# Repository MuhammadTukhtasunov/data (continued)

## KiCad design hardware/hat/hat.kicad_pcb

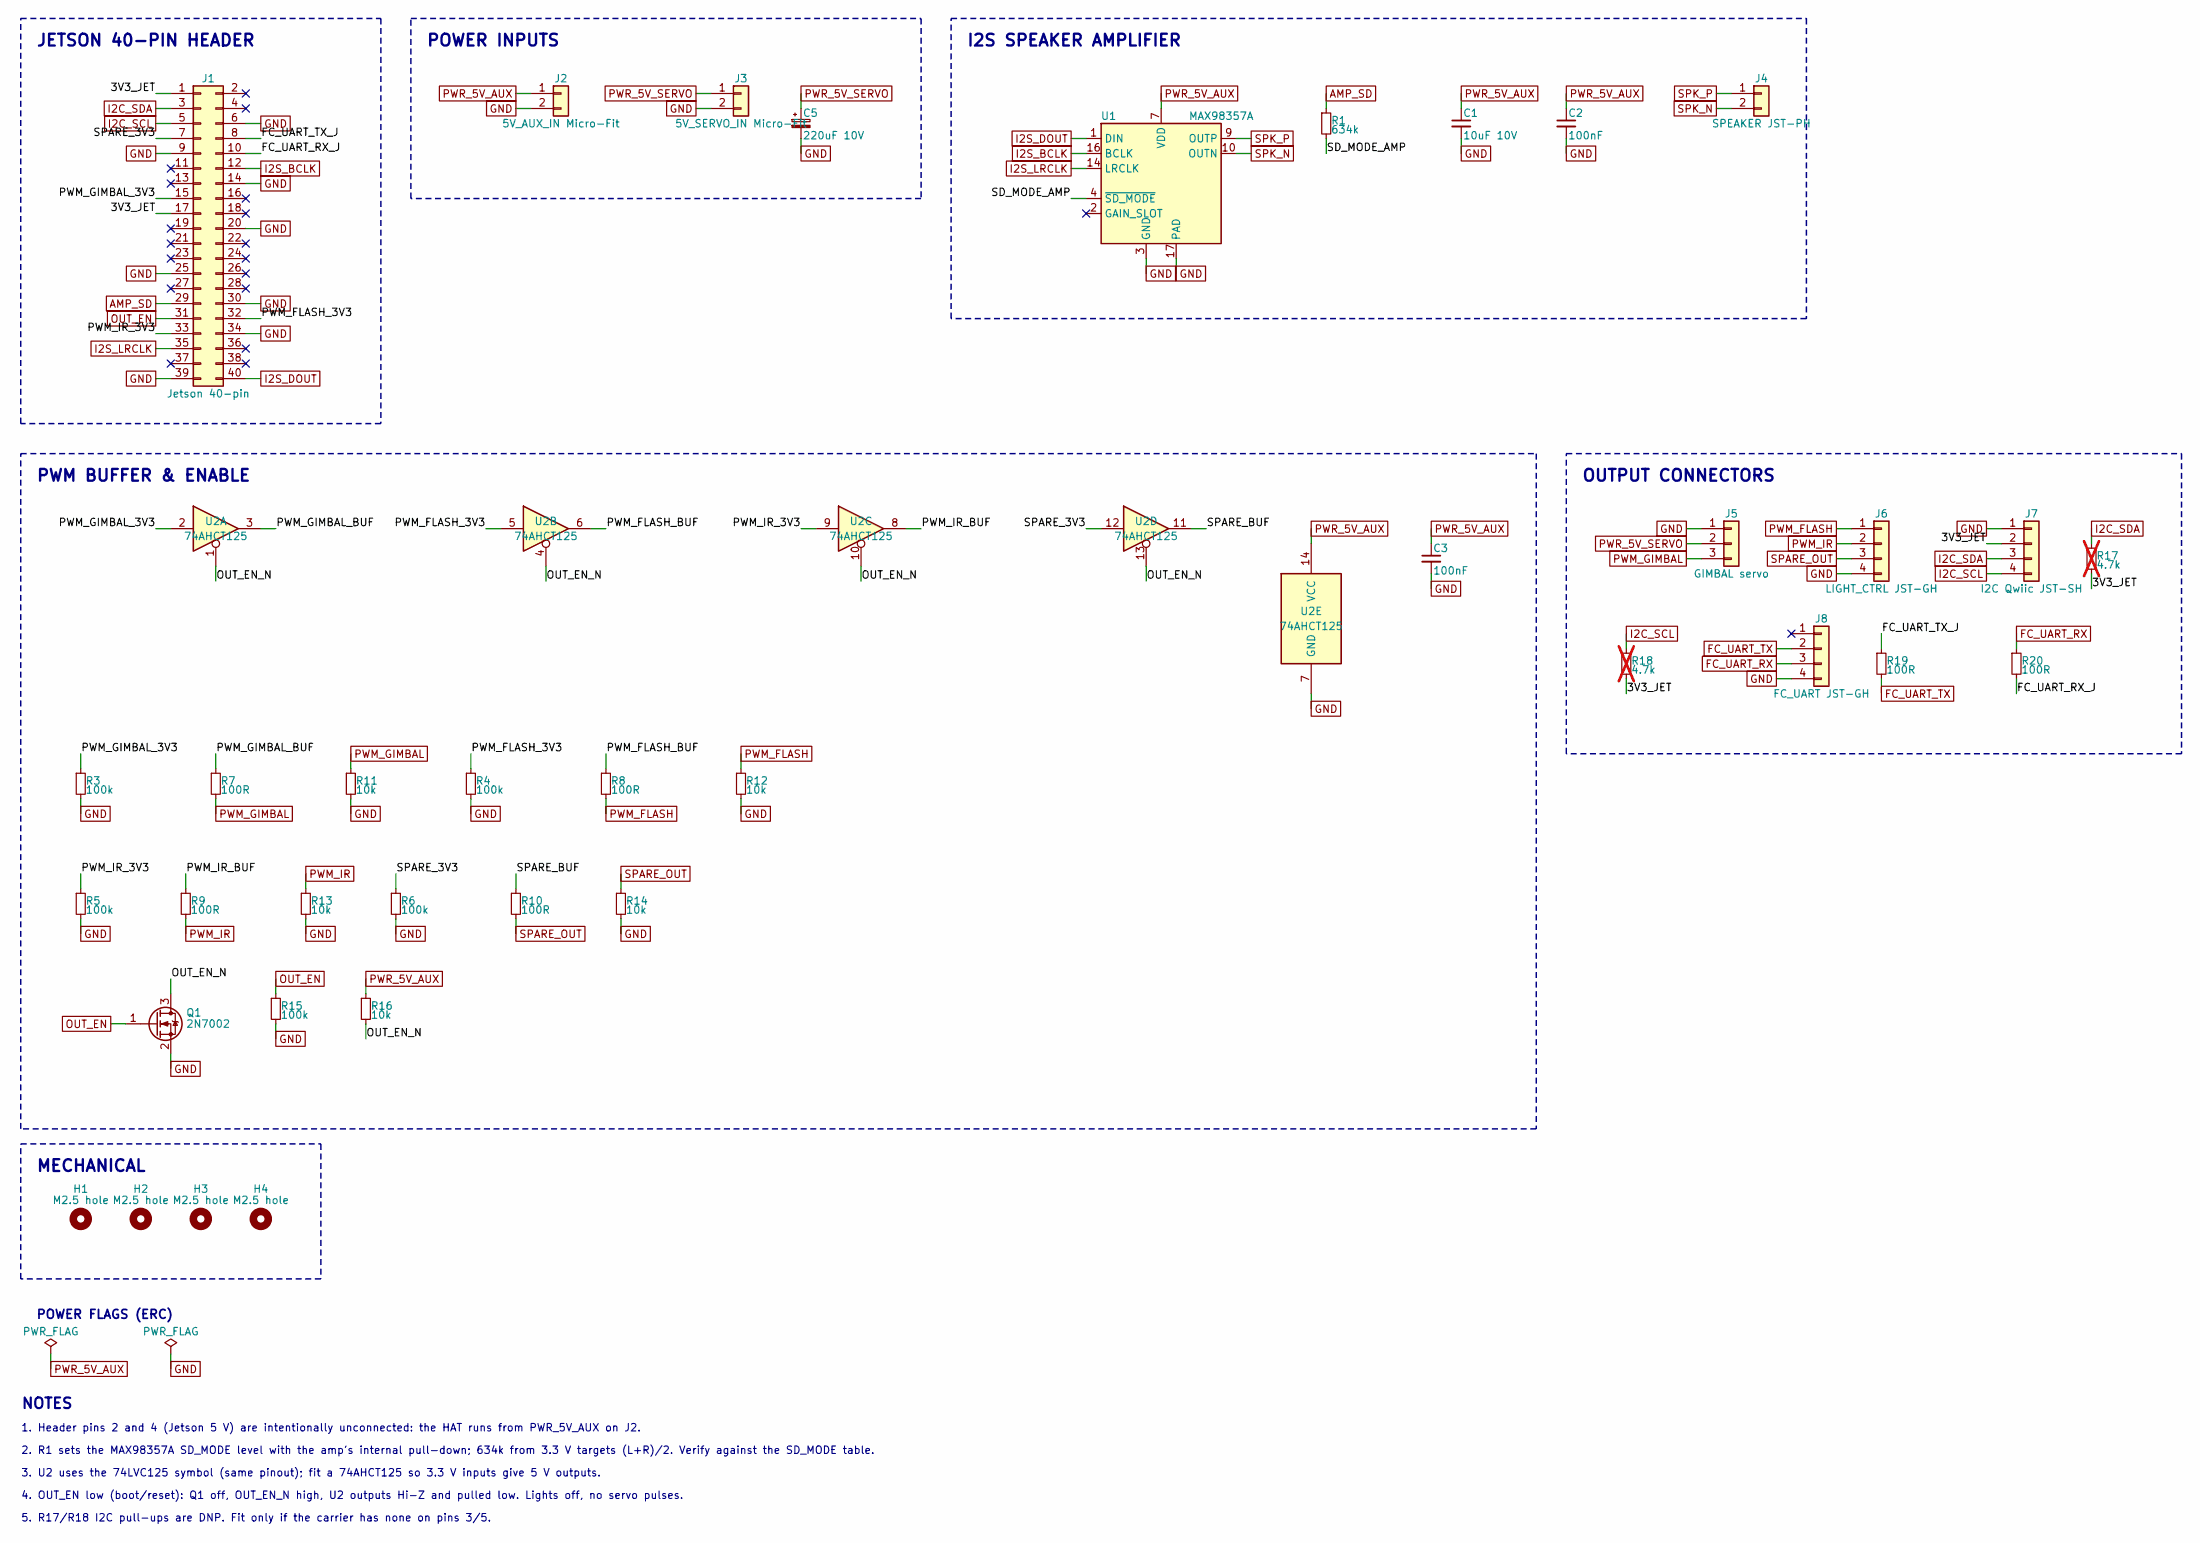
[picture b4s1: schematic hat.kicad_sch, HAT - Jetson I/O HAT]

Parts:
C1: 10uF 10V; C_0805_2012Metric
C2, C3: 100nF; C_0603_1608Metric
C5: 220uF 10V; CP_Elec_8x10.5
H1, H2, H3, H4: M2.5 hole; MountingHole_2.7mm_M2.5
J1: Jetson 40-pin; PinSocket_2x20_P2.54mm_Vertical
J2: 5V_AUX_IN Micro-Fit; Molex_Micro-Fit_3.0_43650-0210_1x02-1MP_P3.00mm_Horizontal
J3: 5V_SERVO_IN Micro-Fit; Molex_Micro-Fit_3.0_43650-0210_1x02-1MP_P3.00mm_Horizontal
J4: SPEAKER JST-PH; JST_PH_S2B-PH-K_1x02_P2.00mm_Horizontal
J5: GIMBAL servo; PinHeader_1x03_P2.54mm_Vertical
J6: LIGHT_CTRL JST-GH; JST_GH_SM04B-GHS-TB_1x04-1MP_P1.25mm_Horizontal
J7: I2C Qwiic JST-SH; JST_SH_SM04B-SRSS-TB_1x04-1MP_P1.00mm_Horizontal
J8: FC_UART JST-GH; JST_GH_SM04B-GHS-TB_1x04-1MP_P1.25mm_Horizontal
Q1: 2N7002; SOT-23
R1: 634k; R_0603_1608Metric
R3, R4, R5, R6, R15: 100k; R_0603_1608Metric
R7, R8, R9, R10, R19, R20: 100R; R_0603_1608Metric
R11, R12, R13, R14, R16: 10k; R_0603_1608Metric
R17, R18: 4.7k; R_0603_1608Metric; not fitted
U1: MAX98357A; TQFN-16-1EP_3x3mm_P0.5mm_EP1.23x1.23mm
U2: 74AHCT125; SOIC-14_3.9x8.7mm_P1.27mm

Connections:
3V3_JET: J1.1, J1.17, J7.2, R17.2, R18.2
AMP_SD: J1.29, R1.1
FC_UART_RX: J8.3, R20.1
FC_UART_RX_J: J1.10, R20.2
FC_UART_TX: J8.2, R19.2
FC_UART_TX_J: J1.8, R19.1
GND: C1.2, C2.2, C3.2, C5.2, J1.6, J1.9, J1.14, J1.20, J1.25, J1.30, J1.34, J1.39, J2.2, J3.2, J5.1, J6.4, J7.1, J8.4, Q1.2 (S), R3.2, R4.2, R5.2, R6.2, R11.2, R12.2, R13.2, R14.2, R15.2, U1.3 (GND), U1.11 (GND), U1.15 (GND), U1.17 (PAD), U2.7 (GND)
I2C_SCL: J1.5, J7.4, R18.1
I2C_SDA: J1.3, J7.3, R17.1
I2S_BCLK: J1.12, U1.16 (BCLK)
I2S_DOUT: J1.40, U1.1 (DIN)
I2S_LRCLK: J1.35, U1.14 (LRCLK)
OUT_EN: J1.31, Q1.1 (G), R15.1
OUT_EN_N: Q1.3 (D), R16.2, U2.1, U2.4, U2.10, U2.13
PWM_FLASH: J6.1, R8.2, R12.1
PWM_FLASH_3V3: J1.32, R4.1, U2.5
PWM_FLASH_BUF: R8.1, U2.6
PWM_GIMBAL: J5.3, R7.2, R11.1
PWM_GIMBAL_3V3: J1.15, R3.1, U2.2
PWM_GIMBAL_BUF: R7.1, U2.3
PWM_IR: J6.2, R9.2, R13.1
PWM_IR_3V3: J1.33, R5.1, U2.9
PWM_IR_BUF: R9.1, U2.8
PWR_5V_AUX: C1.1, C2.1, C3.1, J2.1, R16.1, U1.7 (VDD), U1.8 (VDD), U2.14 (VCC)
PWR_5V_SERVO: C5.1, J3.1, J5.2
SD_MODE_AMP: R1.2, U1.4 (~SD_MODE)
SPARE_3V3: J1.7, R6.1, U2.12
SPARE_BUF: R10.1, U2.11
SPARE_OUT: J6.3, R10.2, R14.1
SPK_N: J4.2, U1.10 (OUTN)
SPK_P: J4.1, U1.9 (OUTP)

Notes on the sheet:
JETSON 40-PIN HEADER
POWER INPUTS
I2S SPEAKER AMPLIFIER
PWM BUFFER & ENABLE
OUTPUT CONNECTORS
MECHANICAL
POWER FLAGS (ERC)
NOTES
1. Header pins 2 and 4 (Jetson 5 V) are intentionally unconnected: the HAT runs from PWR_5V_AUX on J2.
2. R1 sets the MAX98357A SD_MODE level with the amp's internal pull-down; 634k from 3.3 V targets (L+R)/2. Verify against the SD_MODE table.
3. U2 uses the 74LVC125 symbol (same pinout); fit a 74AHCT125 so 3.3 V inputs give 5 V outputs.
4. OUT_EN low (boot/reset): Q1 off, OUT_EN_N high, U2 outputs Hi-Z and pulled low. Lights off, no servo pulses.
5. R17/R18 I2C pull-ups are DNP. Fit only if the carrier has none on pins 3/5.

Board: 2 copper layers, 38 parts (0 on the bottom side), 31 nets, no tracks yet.

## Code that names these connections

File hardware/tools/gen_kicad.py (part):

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              # Raspberry-Pi-HAT style: header centred along the top edge, holes 3.5 mm in
              fixed={"J1": (90, 32.5, 3.5)}, hole_inset=3.5, pack_margin=(2.0, 8.5, 2.0, 7.0))
    b.notes = [
        "Header pins 2 and 4 (Jetson 5 V) are intentionally unconnected: the HAT runs from PWR_5V_AUX on J2.",
        "R1 sets the MAX98357A SD_MODE level with the amp's internal pull-down; 634k from 3.3 V targets (L+R)/2. Verify against the SD_MODE table.",
        "U2 uses the 74LVC125 symbol (same pinout); fit a 74AHCT125 so 3.3 V inputs give 5 V outputs.",
        "OUT_EN low (boot/reset): Q1 off, OUT_EN_N high, U2 outputs Hi-Z and pulled low. Lights off, no servo pulses.",
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    C(k, "C2", "10uF 10V", "PWR_5V_AUX", "GND", C0805)

    k = b.block("Teensy 4.1", cols=1)
    tp = {teensy_pin("VIN"): "PWR_5V_AUX", "1": "GND", "34": "GND", "47": "GND",
          "15": "3V3_T", "46": "3V3_T",
          teensy_pin("D18"): "SNS_SDA", teensy_pin("D19"): "SNS_SCL",
          teensy_pin("D2"): "GPIO2", teensy_pin("D3"): "GPIO3"}
    for n in range(1, 9):
        tp[teensy_pin(tx[n])] = f"TX{n}"
        tp[teensy_pin(rx[n])] = f"RX{n}_B"
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
    k = b.block("Expansion", cols=3)
    CONN(k, "J10", "EXP", "Connector_PinHeader_2.54mm:PinHeader_1x06_P2.54mm_Vertical",
         ["3V3_T", "GND", "SNS_SDA", "SNS_SCL", "GPIO2", "GPIO3"])
    R(k, "R41", "4.7k", "SNS_SDA", "3V3_T", dnp=True)
    R(k, "R42", "4.7k", "SNS_SCL", "3V3_T", dnp=True)

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
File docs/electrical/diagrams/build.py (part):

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    end''')
    e = d.edge
    e("P_I2S", "U1", "I2S_BCLK · I2S_LRCLK · I2S_DOUT", "i2s")
    e("P_AMP", "RSD", "AMP_SD", "gpio")
    e("RSD", "U1", "SD_MODE", "gpio")
    e("U1", "J4", "SPK_P / SPK_N (BTL)", "power")
    e("P_PWM", "RPD", "PWM_GIMBAL_3V3 · PWM_FLASH_3V3 · PWM_IR_3V3", "pwm")
    e("P_SP", "RPD", "SPARE_3V3", "gpio")
    e("RPD", "U2", "1A–4A", "pwm")
    e("P_EN", "Q1", "OUT_EN", "gpio")
    e("Q1", "U2", "OUT_EN_N → 1OE#–4OE#", "gpio")
    e("U2", "ROUT", "1Y–4Y (5 V)", "pwm")
    e("ROUT", "J5", "PWM_GIMBAL", "pwm")
    e("ROUT", "J6", "PWM_FLASH · PWM_IR · SPARE_OUT", "pwm")
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
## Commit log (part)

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2026-06-12 Add localai-site: static marketing site for local AI consulting
    Complete single-page site with datasheet-style identity: hero with
    animated data-perimeter schematic, eight service modules, four-step
    process, local-vs-cloud comparison table, about, three engagement
    tiers, FAQ, and contact form. Self-hosted fonts (Archivo + IBM Plex
    Mono), zero external requests with a live request-counter badge,
    JSON-LD LocalBusiness/ProfessionalService schema, sitemap, robots.txt,
2026-06-12 Add GitHub Pages deploy workflow for localai-site
    https://claude.ai/code/session_018aHQ2jGQStQqshVmWX1PV3
2026-06-30 Make Pages deploy manual-only so it stops failing on every push
    The deploy workflow can only run after GitHub Pages is enabled once in
    repo settings (Source: GitHub Actions). The build token cannot enable it
    automatically, so auto-running on push only produced a failing check.
    Switch to workflow_dispatch so the PR stays green; run it by hand after
    enabling Pages.
    https://claude.ai/code/session_018aHQ2jGQStQqshVmWX1PV3
2026-06-30 Clarify deploy steps: GitHub Pages needs one-time manual enable
    Document that the Pages site must be enabled once in Settings -> Pages
    (Source: GitHub Actions) before the deploy workflow can run, and that the
    'Resource not accessible by integration' error only means Pages is not
    enabled yet. Add Netlify Drop as the no-settings alternative.
    https://claude.ai/code/session_018aHQ2jGQStQqshVmWX1PV3
